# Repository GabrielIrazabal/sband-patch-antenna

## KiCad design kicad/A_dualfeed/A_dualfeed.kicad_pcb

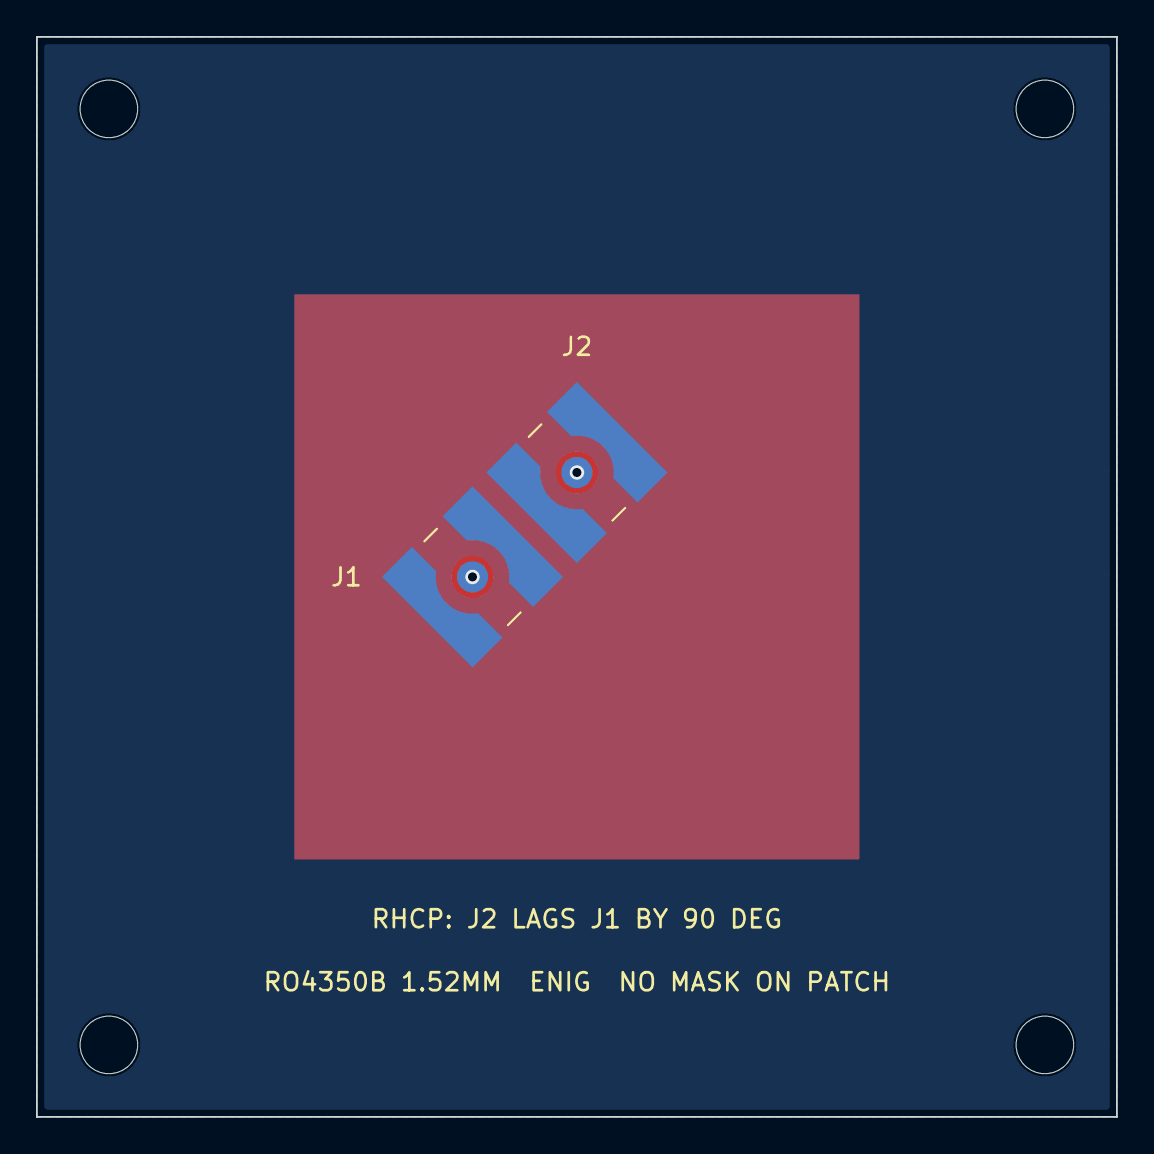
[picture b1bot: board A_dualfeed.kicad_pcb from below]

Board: 2 copper layers, 60.0 x 60.0 mm, 6 parts (2 on the bottom side), 2 nets, no tracks yet.

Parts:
H1, H2, H3, H4: MountingHole_3.2mm_M3
J1, J2: Wurth WR-SMA 60312102114405; SMA_Wurth_60312102114405_Vertical

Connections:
GND: J1.2, J2.2
PATCH: J1.1, J2.1
